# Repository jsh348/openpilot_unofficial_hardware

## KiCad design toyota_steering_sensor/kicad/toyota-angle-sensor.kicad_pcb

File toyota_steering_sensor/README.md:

Packing all the electronics from the [Zorro Sensor](https://github.com/zorrobyte/betterToyotaAngleSensorForOP) all on one board.

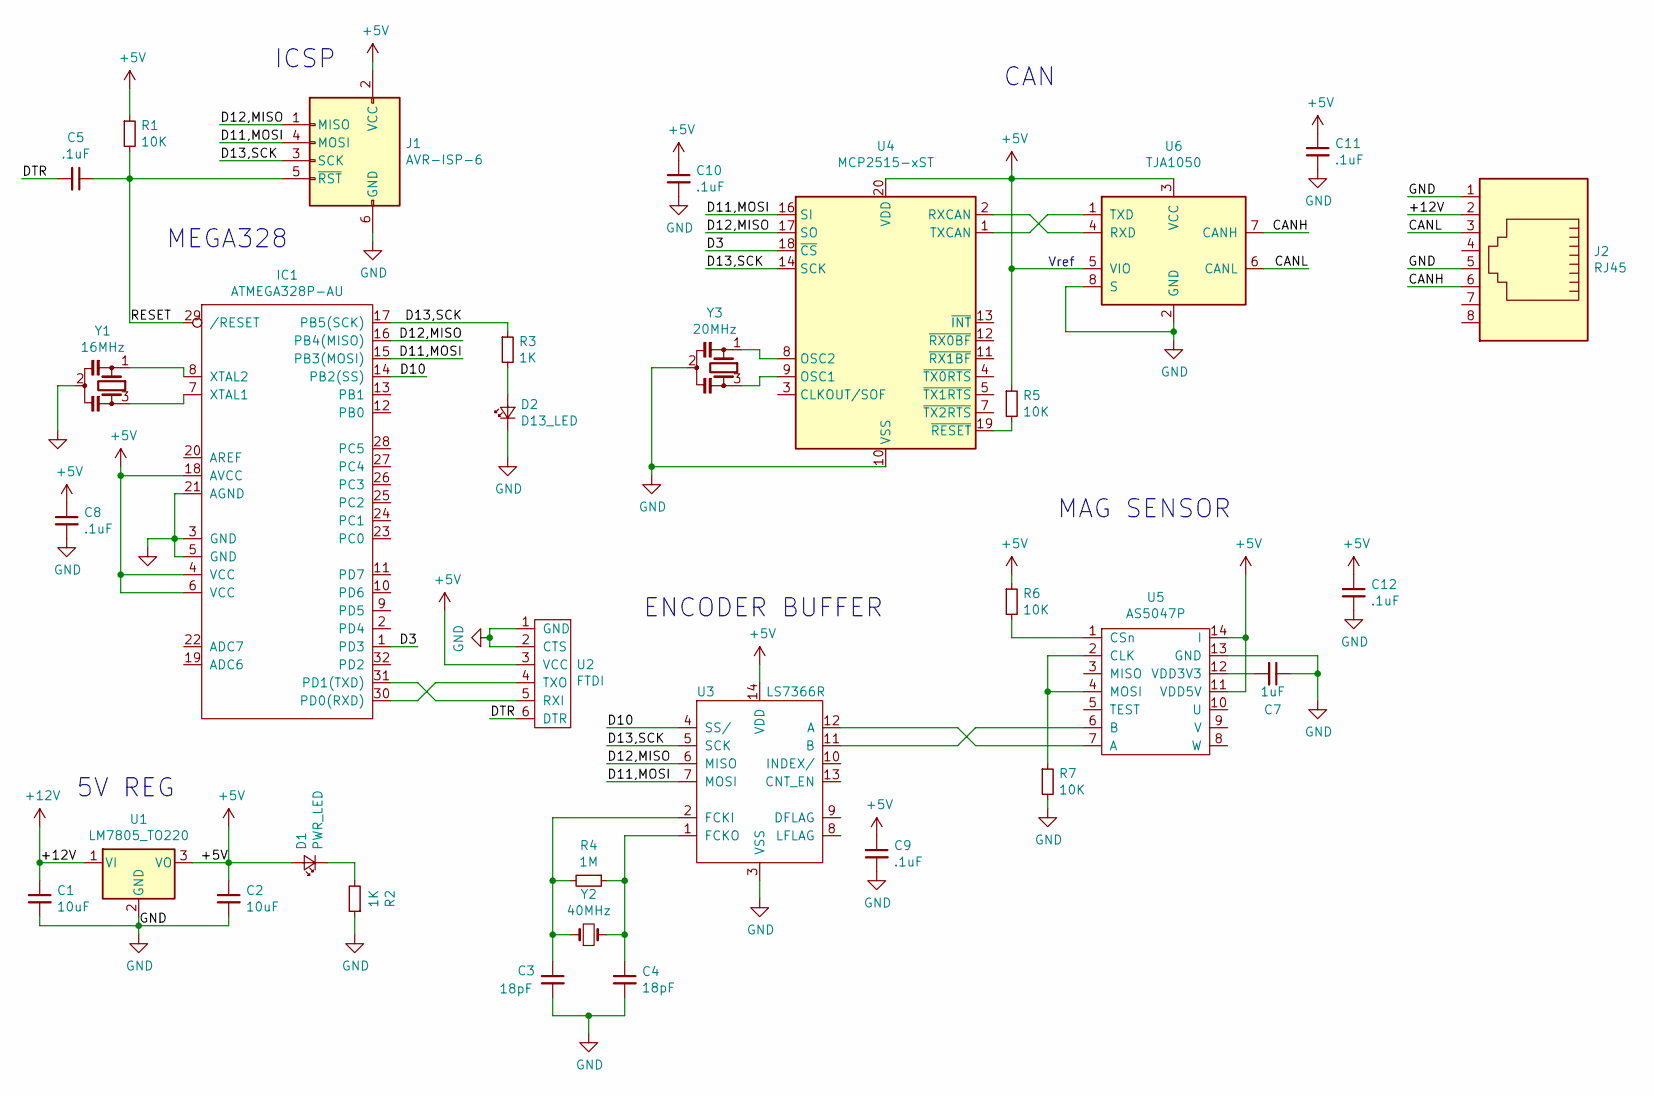
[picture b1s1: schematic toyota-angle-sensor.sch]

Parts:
C1, C2: 10uF; C_1210_3225Metric; Digi-Key Part Number 490-14536-1-ND
C3, C4: 18pF; C_0603_1608Metric; Digi-Key Part Number 1276-2208-1-ND
C5: .1uF; C_0603_1608Metric
C7: 1uF; C_0603_1608Metric; Digi-Key Part Number 490-12297-1-ND
C8, C9, C10, C11, C12: .1uF; C_0603_1608Metric; Digi-Key Part Number 1276-1000-1-ND
D1: PWR_LED; LED_0805_2012Metric; Digi-Key Part Number 475-1410-1-ND
D2: D13_LED; LED_0805_2012Metric; Digi-Key Part Number 475-1410-1-ND
IC1: ATMEGA328P-AU; TQFP-32_7x7mm_P0.8mm
J1: AVR-ISP-6; PinHeader_2x03_P2.54mm_Vertical; Digi-Key Part Number N/A
J2: RJ45; Molex 855025008 RJ45; Digi-Key Part Number 609-1046-ND
R1, R5, R6, R7: 10K; R_0603_1608Metric; Digi-Key Part Number A130097CT-ND
R2, R3: 1K; R_0603_1608Metric; Digi-Key Part Number A130091CT-ND
R4: 1M; R_0603_1608Metric; Digi-Key Part Number A130109CT-ND
U1: LM7805_TO220; TO-220-3_Vertical
U2: FTDI; PinHeader_1x06_P1.27mm_Vertical_SMD_Pin1Left
U3: LS7366R; TSSOP-14_4.4x5mm_P0.65mm; Digi-Key Part Number N/A
U4: MCP2515-xST; TSSOP-20_4.4x6.5mm_P0.65mm
U5: AS5047P; TSSOP-14_4.4x5mm_P0.65mm; Digi-Key Part Number AS5047P-ATSMCT-ND
U6: TJA1050; SOIC-8_3.9x4.9mm_P1.27mm; Digi-Key Part Number 568-10292-1-ND
Y1: 16MHz; Resonator_SMD_muRata_CSTxExxV-3Pin_3.0x1.1mm; Digi-Key Part Number 490-17948-1-ND
Y2: 40MHz; Crystal_SMD_Abracon_ABM3-2Pin_5.0x3.2mm
Y3: 20MHz; Resonator_SMD_muRata_CSTxExxV-3Pin_3.0x1.1mm

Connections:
+5V: C2.1, C8.1, C9.1, C10.1, C11.1, C12.1, D1.2 (A), IC1.4 (VCC), IC1.6 (VCC), IC1.18 (AVCC), J1.2 (VCC), R1.1, R5.1, R6.1, U1.3 (VO), U2.3 (VCC), U3.14 (VDD), U4.20 (VDD), U5.11 (VDD5V), U5.14 (I), U6.3 (VCC), U6.5 (VIO)
+12V: C1.1, J2.2, U1.1 (VI)
/CANH: J2.6, U6.7 (CANH)
/CANL: J2.3, U6.6 (CANL)
/D3: IC1.1 (PD3), U4.18 (~CS)
/D10: IC1.14 (PB2(SS)), U3.4 (SS/)
/D11,MOSI: IC1.15 (PB3(MOSI)), J1.4 (MOSI), U3.7 (MOSI), U4.16 (SI)
/D12,MISO: IC1.16 (PB4(MISO)), J1.1 (MISO), U3.6 (MISO), U4.17 (SO)
/D13,SCK: IC1.17 (PB5(SCK)), J1.3 (SCK), R3.1, U3.5 (SCK), U4.14 (SCK)
/DTR: C5.2, U2.6 (DTR)
/RESET: C5.1, IC1.29 (/RESET), J1.5 (~RST), R1.2
GND: C1.2, C2.2, C3.2, C4.2, C7.1, C8.2, C9.2, C10.2, C11.2, C12.2, D2.1 (K), IC1.3 (GND), IC1.5 (GND), IC1.21 (AGND), J1.6 (GND), J2.1, J2.5, R2.1, R7.2, U1.2 (GND), U2.1 (GND), U2.2 (CTS), U3.3 (VSS), U4.10 (VSS), U5.13 (GND), U6.2 (GND), U6.8 (S), Y1.2, Y3.2
unnamed: C3.1, R4.2, U3.2 (FCKI), Y2.1
unnamed: C4.1, R4.1, U3.1 (FCKO), Y2.2
unnamed: C7.2, U5.12 (VDD3V3)
unnamed: D1.1 (K), R2.2
unnamed: D2.2 (A), R3.2
unnamed: IC1.7 (XTAL1), Y1.3
unnamed: IC1.8 (XTAL2), Y1.1
unnamed: IC1.30 (PD0(RXD)), U2.4 (TXO)
unnamed: IC1.31 (PD1(TXD)), U2.5 (RXI)
unnamed: R5.2, U4.19 (~RESET)
unnamed: R6.2, U5.1 (CSn)
unnamed: R7.1, U5.2 (CLK), U5.4 (MOSI)
unnamed: U3.11 (B), U5.6 (B)
unnamed: U3.12 (A), U5.7 (A)
unnamed: U4.1 (TXCAN), U6.1 (TXD)
unnamed: U4.2 (RXCAN), U6.4 (RXD)
unnamed: U4.8 (OSC2), Y3.1
unnamed: U4.9 (OSC1), Y3.3

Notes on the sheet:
ICSP
5V REG
CAN
Vref
ENCODER BUFFER
MEGA328
MAG SENSOR

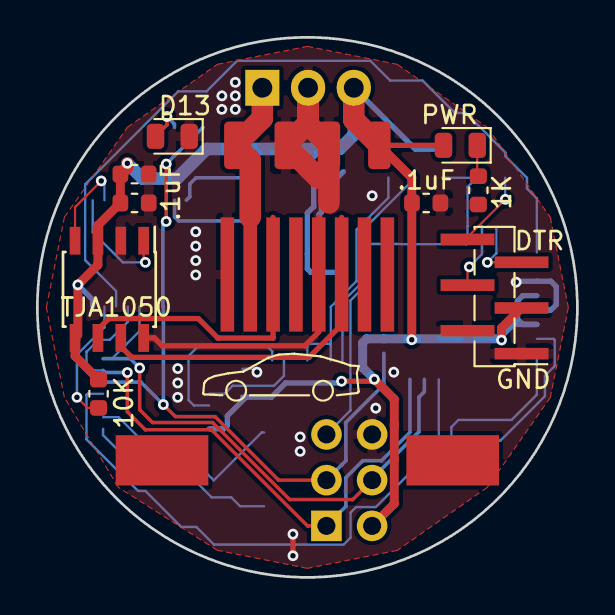
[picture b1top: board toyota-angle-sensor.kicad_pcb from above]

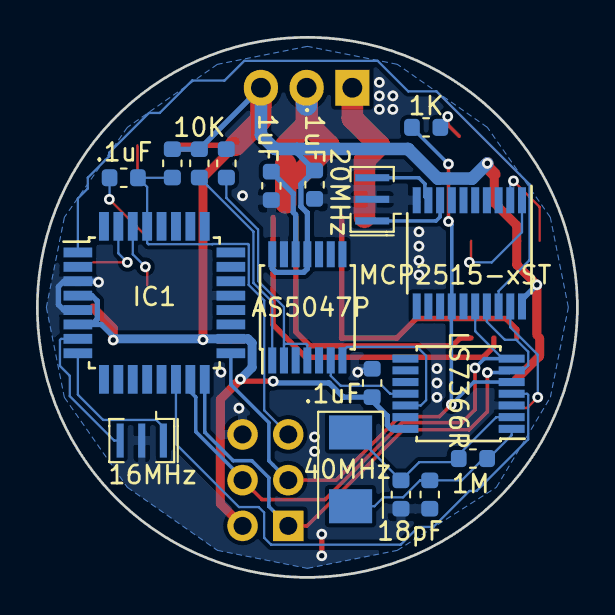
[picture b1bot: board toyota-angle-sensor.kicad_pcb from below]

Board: 2 copper layers, 30.0 x 30.0 mm, 32 parts (19 on the bottom side), 30 nets.

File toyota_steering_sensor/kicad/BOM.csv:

"Item","Qty","Reference(s)","Value","LibPart","Footprint","Datasheet","Digi-Key Part Number"
"1","2","C1, C2","10uF","Device:C_Small","Capacitor_SMD:C_1210_3225Metric","~","490-14536-1-ND"
"2","2","C3, C4","18pF","Device:C_Small","Capacitor_SMD:C_0603_1608Metric","~","1276-2208-1-ND"
"3","2","C5, C6","27pF","Device:C_Small","Capacitor_SMD:C_0603_1608Metric","~","1276-1086-1-ND "
"4","1","C7","1uF","Device:C_Small","Capacitor_SMD:C_0603_1608Metric","~","1276-1102-1-ND"
"5","5","C8, C9, C10, C11, C12",".1uF","Device:C_Small","Capacitor_SMD:C_0603_1608Metric","~","1276-1000-1-ND"
"6","1","D1","PWR_LED","Device:LED_Small","LED_SMD:LED_0805_2012Metric","~","475-1410-1-ND"
"7","1","D2","D13_LED","Device:LED_Small","LED_SMD:LED_0805_2012Metric","~","475-1410-1-ND"
"8","1","J1","AVR-ISP-6","Connector:AVR-ISP-6","Connector_PinHeader_2.54mm:PinHeader_2x03_P2.54mm_Vertical"," ~","N/A"
"9","1","J2","RJ45","Connector:RJ45","Connector_RJ:RJ45_Amphenol_54602-x08_Horizontal","~","609-1046-ND"
"10","4","R1, R5, R6, R7","10K","Device:R_Small","Resistor_SMD:R_0603_1608Metric","~","A130097CT-ND"
"11","2","R2, R3","1K","Device:R_Small","Resistor_SMD:R_0603_1608Metric","~","A130091CT-ND "
"12","1","R4","1M","Device:R_Small","Resistor_SMD:R_0603_1608Metric","~","A130109CT-ND "
"13","1","U1","NCP1117-5.0_SOT223","Regulator_Linear:NCP1117-5.0_SOT223","Package_TO_SOT_SMD:SOT-223-3_TabPin2","http://www.onsemi.com/pub_link/Collateral/NCP1117-D.PDF","NCP1117ST50T3GOSCT-ND"
"14","1","U2","ATMEGA328PB-AU","Angle_Sensor:ATMEGA328PB-AU","Package_QFP:TQFP-32_7x7mm_P0.8mm","","ATMEGA328PB-AU-ND"
"15","1","U3","LS7366R","Angle_Sensor:LS7366R","Package_SO:SOIC-14_3.9x8.7mm_P1.27mm","","N/A"
"16","1","U4","MCP2515-xSO","Interface_CAN_LIN:MCP2515-xSO","Package_SO:SOIC-18W_7.5x11.6mm_P1.27mm","http://ww1.microchip.com/downloads/en/DeviceDoc/21801e.pdf","MCP2515T-I/SOCT-ND"
"17","1","U5","AS5047P","Angle_Sensor:AS5047P","Package_SO:TSSOP-14_4.4x5mm_P0.65mm","","AS5047P-ATSMCT-ND"
"18","1","U6","TJA1050","Interface_CAN_LIN:TJA1051T-3","Package_SO:SOIC-8_3.9x4.9mm_P1.27mm","http://www.nxp.com/documents/data_sheet/TJA1051.pdf","568-10292-1-ND"
"19","1","Y1","16MHz","Device:Resonator_Small","Crystal:Resonator_SMD_muRata_CSTxExxV-3Pin_3.0x1.1mm_HandSoldering","~","490-17948-1-ND"
"20","1","Y2","40MHz","Device:Crystal_GND24","Crystal:Crystal_SMD_Abracon_ABM8G-4Pin_3.2x2.5mm","~","535-13401-1-ND"
"21","1","Y3","8MHz","Device:Crystal_Small","Crystal:Crystal_SMD_Abracon_ABM3-2Pin_5.0x3.2mm_HandSoldering","~","535-10630-1-ND"

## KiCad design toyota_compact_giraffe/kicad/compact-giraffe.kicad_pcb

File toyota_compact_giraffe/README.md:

Stealth giraffe for Toyota
==========================

Replacement for the [Toyota giraffe](https://comma.ai/shop/products/giraffe) which could be hidden under the camera cover

Build
=====
https://youtu.be/VyTzIEMhPvQ

Materials
---------
* [Harness](https://www.amazon.com/gp/product/B01EUZ8TPI/)
* EON USB cable or [USB extension cable](https://www.amazon.com/gp/product/B002KKYXSI)
* 120 Ohm 1206 chip resistor

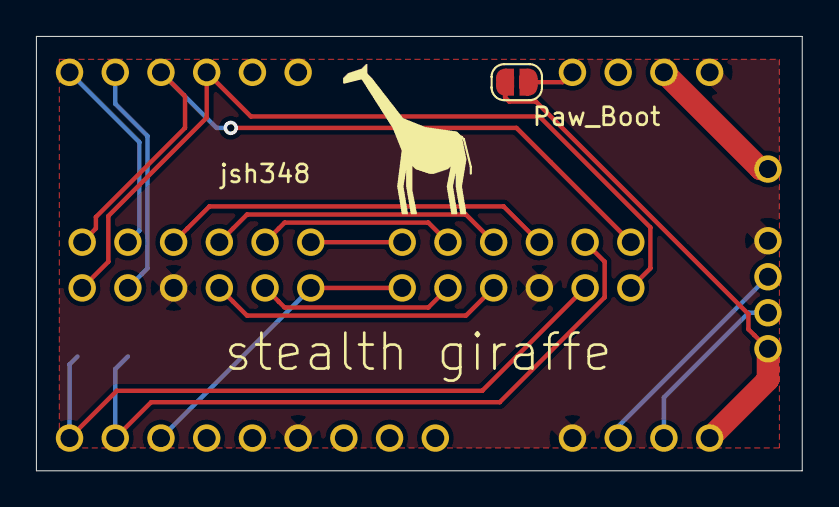
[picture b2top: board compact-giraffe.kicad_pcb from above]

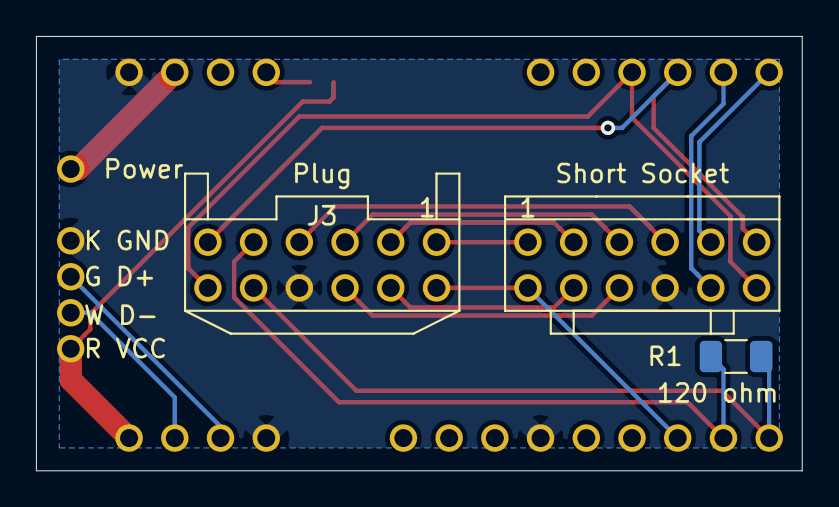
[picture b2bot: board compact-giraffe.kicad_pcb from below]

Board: 2 copper layers, 42.5 x 24.1 mm, 7 parts (6 on the bottom side), 19 nets.

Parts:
J2, J3: MOBILEEYE; MobilEye
JP1: Paw_Boot; SolderJumper-2_P1.3mm_Open_RoundedPad1.0x1.5mm
P1: panda
R1: 120 ohm; R_1206_3216Metric
U1: Power; 12VIN
U2: USB

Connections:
/2: J2.2, J3.2
/3: J2.3, J3.3
/4: J2.4, J3.4
/5V: JP1.1, P1.1, U2.1
/8: J2.8, J3.8
/9: J2.9, J3.9
/12VIN: P1.15, U1.~
/CAN1_H: J2.5, P1.23
/CAN1_H': J3.5, P1.12, R1.2
/CAN1_L: J2.11, P1.22
/CAN1_L': J3.11, P1.13, R1.1
/CAN2_H: J2.6, J3.6, P1.21
/CAN2_L: J2.12, J3.12, P1.20
/D+: P1.3, U2.3
/D-: P1.2, U2.2
/DFU: JP1.2, P1.17
/GND: J2.10, J3.10, P1.4, P1.8, P1.14, U2.4
/HTR: J2.1, J3.1
/IGN: J2.7, J3.7, P1.11

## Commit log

2019-08-03 fixed USB D+ D- flip
2019-08-03 add pics
2019-08-03 add sch pdf
2019-08-03 add README
2019-08-06 new board design
2019-08-10 add gerber
2019-08-10 reorganize dir, now multiple projects in repo
2019-08-10 added prject: steering sensor (ZSS compact)
2019-08-10 moved atmega chip slightly to pass design rule check
2019-08-10 modify text
2019-08-10 add gitignore in steering sensor dir
2019-08-10 change texts on board
2019-08-10 added gerber
2019-08-10 generate schematic pdf
2019-08-10 moved gerber zip to where it belongs
2019-08-10 reorganize files for compact giraffe
2019-08-10 change fill tolerance
2019-08-10 silk screen text adjustments
2019-08-10 generate gerber
2019-08-10 added readme for steering sensor
2019-08-10 changed texts on board, regenerate gerber
2019-08-10 change resistor and capacitor from 0402 to 0603
2019-08-10 modified silkscreen to show resistance and capacitance, regen gerber
2019-08-10 flip back side to front, regen gerber
2019-08-10 modify silkscreen text for angle sensor, added graphics, regen gerber
2019-08-19 modified component ref for BOM
2019-08-20 modifications for v3. trace width, re-routs for easier 12v soldering
2019-08-30 update giraffe readme - added video
2019-09-05 added smd RJ45 footprint to save space
2019-09-05 add V2 todo outline
2019-09-05 modified sch according to V2Changes.txt
2019-09-06 shrink and re-route pcb. not done yet
2019-09-09 consolidate gitignore
2019-09-09 done routing v2
2019-09-11 pcb v2 done
2019-09-11 update silk screen
2019-09-11 update gitignore
2019-09-23 updated BOM for V2
